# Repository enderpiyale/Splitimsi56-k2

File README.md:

# Splitimsi
 Regular keeb that can split

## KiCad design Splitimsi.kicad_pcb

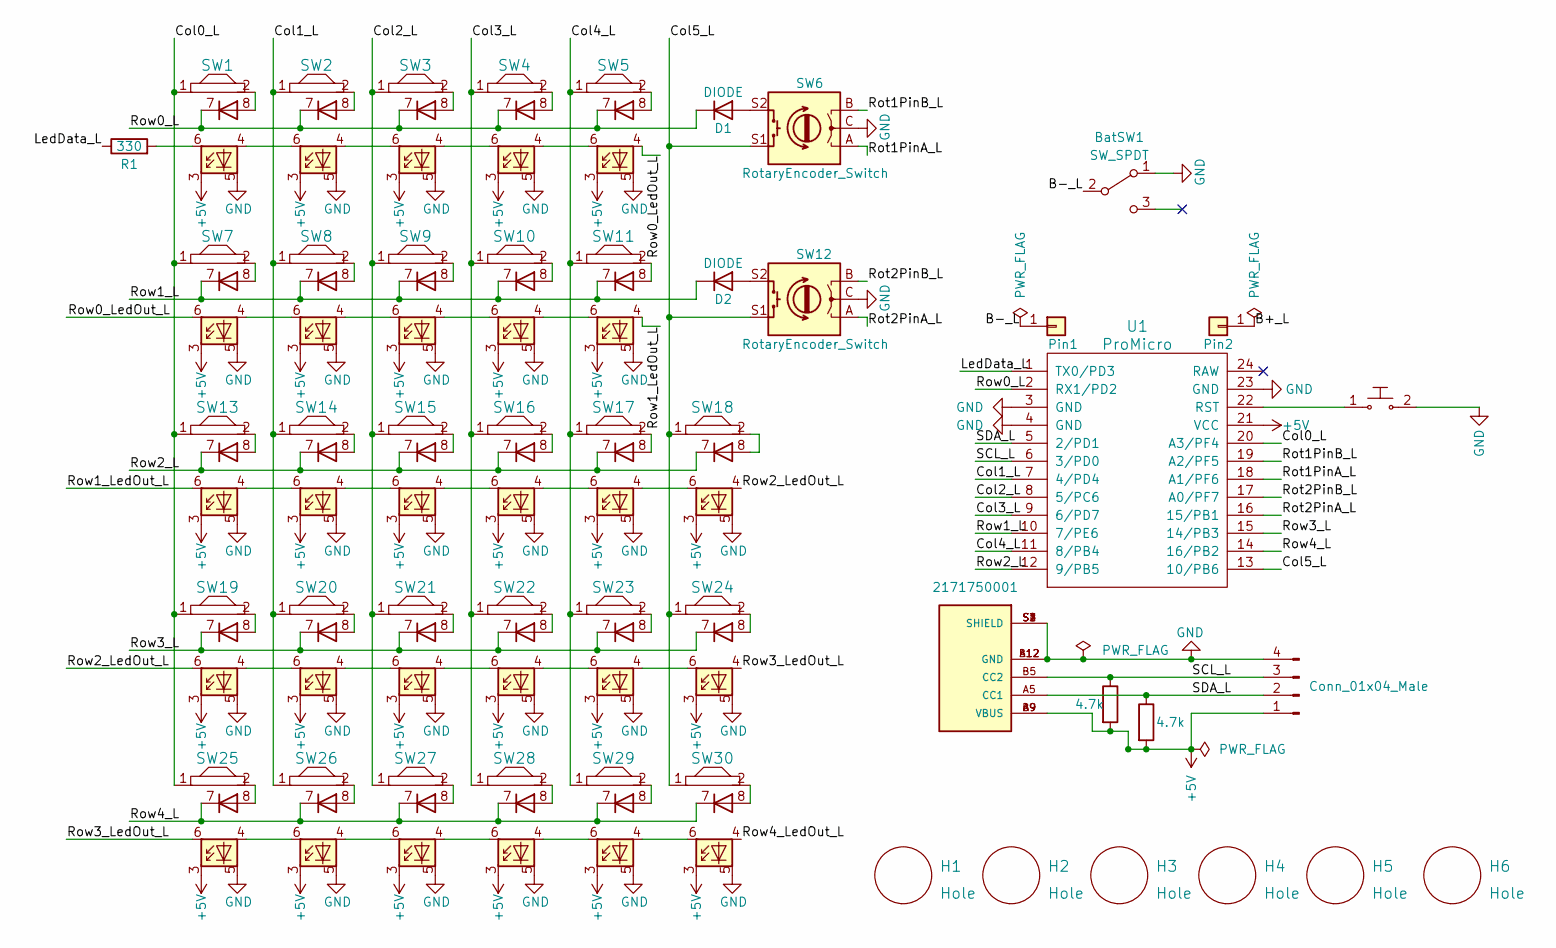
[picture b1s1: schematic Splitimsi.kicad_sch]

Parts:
BatSW1: SW_SPDT; MSK12C02
D1, D2: DIODE; D_SOD123
Dogo1: Conn_01x04_Male; PinSocket_1x04_P2.00mm_Vertical
H1, H2, H3, H4, H5, H6: Hole; Generic-Mounthole
J1: 2171750001; MOLEX_2171750001; PARTREV A1
Pin1, Pin2: Conn_01x01; SinglePad
R1: 330; R_1206_3216Metric_Pad1.30x1.75mm_HandSolder
R2, R3: 4.7k; R_1206_3216Metric_Pad1.30x1.75mm_HandSolder
SW1, SW2, SW3, SW4, SW7, SW8, SW9, SW10, SW11, SW13, SW14, SW15, SW16, SW17, SW18, SW19, SW20, SW21, SW22, SW23, SW24, SW25, SW26, SW27, SW28, SW29, SW30: MX_RGB; Kailh_HS_MX_LED
SW5: MX_RGB; Kailh_HS_MX_LED_option4
SW6, SW12: RotaryEncoder_Switch; RotaryEncoder_EC11
U1: ProMicro; ArduinoProMicro
rst1: MPN B3U-1000P; Digi-Key_PN SW1020CT-ND

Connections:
+5V: Dogo1.1, J1.A9 (VBUS), J1.B9 (VBUS), R2.2, R3.2, SW1.3 (VDD), SW2.3 (VDD), SW3.3 (VDD), SW4.3 (VDD), SW5.3 (VDD), SW7.3 (VDD), SW8.3 (VDD), SW9.3 (VDD), SW10.3 (VDD), SW11.3 (VDD), SW13.3 (VDD), SW14.3 (VDD), SW15.3 (VDD), SW16.3 (VDD), SW17.3 (VDD), SW18.3 (VDD), SW19.3 (VDD), SW20.3 (VDD), SW21.3 (VDD), SW22.3 (VDD), SW23.3 (VDD), SW24.3 (VDD), SW25.3 (VDD), SW26.3 (VDD), SW27.3 (VDD), SW28.3 (VDD), SW29.3 (VDD), SW30.3 (VDD), U1.21 (VCC)
/B+_L: Pin2.1
/B-_L: BatSW1.2 (B), Pin1.1
/Col0_L: SW1.1, SW7.1, SW13.1, SW19.1, SW25.1, U1.20 (A3/PF4)
/Col1_L: SW2.1, SW8.1, SW14.1, SW20.1, SW26.1, U1.7 (4/PD4)
/Col2_L: SW3.1, SW9.1, SW15.1, SW21.1, SW27.1, U1.8 (5/PC6)
/Col3_L: SW4.1, SW10.1, SW16.1, SW22.1, SW28.1, U1.9 (6/PD7)
/Col4_L: SW5.1, SW11.1, SW17.1, SW23.1, SW29.1, U1.11 (8/PB4)
/Col5_L: SW6.S1, SW12.S1, SW18.1, SW24.1, SW30.1, U1.13 (10/PB6)
/LedData_L: R1.1, U1.1 (TX0/PD3)
/Rot1PinA_L: SW6.A, U1.18 (A1/PF6)
/Rot1PinB_L: SW6.B, U1.19 (A2/PF5)
/Rot2PinA_L: SW12.A, U1.16 (15/PB1)
/Rot2PinB_L: SW12.B, U1.17 (A0/PF7)
/Row0_L: D1.2 (K), SW1.7 (K), SW2.7 (K), SW3.7 (K), SW4.7 (K), SW5.7 (K), U1.2 (RX1/PD2)
/Row0_LedOut_L: SW5.4 (DOUT), SW7.6 (DIN)
/Row1_L: D2.2 (K), SW7.7 (K), SW8.7 (K), SW9.7 (K), SW10.7 (K), SW11.7 (K), U1.10 (7/PE6)
/Row1_LedOut_L: SW11.4 (DOUT), SW13.6 (DIN)
/Row2_L: SW13.7 (K), SW14.7 (K), SW15.7 (K), SW16.7 (K), SW17.7 (K), SW18.7 (K), U1.12 (9/PB5)
/Row2_LedOut_L: SW18.4 (DOUT), SW19.6 (DIN)
/Row3_L: SW19.7 (K), SW20.7 (K), SW21.7 (K), SW22.7 (K), SW23.7 (K), SW24.7 (K), U1.15 (14/PB3)
/Row3_LedOut_L: SW24.4 (DOUT), SW25.6 (DIN)
/Row4_L: SW25.7 (K), SW26.7 (K), SW27.7 (K), SW28.7 (K), SW29.7 (K), SW30.7 (K), U1.14 (16/PB2)
/Row4_LedOut_L: SW30.4 (DOUT)
/SCL_L: Dogo1.3, J1.B5 (CC2), R2.1, U1.6 (3/PD0)
/SDA_L: Dogo1.2, J1.A5 (CC1), R3.1, U1.5 (2/PD1)
GND: BatSW1.1 (A), Dogo1.4, J1.A12 (GND), J1.B12 (GND), J1.S1 (SHIELD), J1.S2 (SHIELD), J1.S3 (SHIELD), J1.S4 (SHIELD), SW1.5 (GND), SW2.5 (GND), SW3.5 (GND), SW4.5 (GND), SW5.5 (GND), SW6.C, SW7.5 (GND), SW8.5 (GND), SW9.5 (GND), SW10.5 (GND), SW11.5 (GND), SW12.C, SW13.5 (GND), SW14.5 (GND), SW15.5 (GND), SW16.5 (GND), SW17.5 (GND), SW18.5 (GND), SW19.5 (GND), SW20.5 (GND), SW21.5 (GND), SW22.5 (GND), SW23.5 (GND), SW24.5 (GND), SW25.5 (GND), SW26.5 (GND), SW27.5 (GND), SW28.5 (GND), SW29.5 (GND), SW30.5 (GND), U1.3 (GND), U1.4 (GND), U1.23 (GND), rst1.2
unnamed: D1.1 (A), SW6.S2
unnamed: D2.1 (A), SW12.S2
unnamed: R1.2, SW1.6 (DIN)
unnamed: SW1.2, SW1.8 (A)
unnamed: SW1.4 (DOUT), SW2.6 (DIN)
unnamed: SW2.2, SW2.8 (A)
unnamed: SW2.4 (DOUT), SW3.6 (DIN)
unnamed: SW3.2, SW3.8 (A)
unnamed: SW3.4 (DOUT), SW4.6 (DIN)
unnamed: SW4.2, SW4.8 (A)
unnamed: SW4.4 (DOUT), SW5.6 (DIN)
unnamed: SW5.2, SW5.8 (A)
unnamed: SW7.2, SW7.8 (A)
unnamed: SW7.4 (DOUT), SW8.6 (DIN)
unnamed: SW8.2, SW8.8 (A)
unnamed: SW8.4 (DOUT), SW9.6 (DIN)
unnamed: SW9.2, SW9.8 (A)
unnamed: SW10.2, SW10.8 (A)
unnamed: SW10.4 (DOUT), SW11.6 (DIN)
unnamed: SW9.4 (DOUT), SW10.6 (DIN)
unnamed: SW11.2, SW11.8 (A)
unnamed: SW13.2, SW13.8 (A)
unnamed: SW13.4 (DOUT), SW14.6 (DIN)
unnamed: SW14.2, SW14.8 (A)
unnamed: SW14.4 (DOUT), SW15.6 (DIN)
unnamed: SW15.2, SW15.8 (A)
unnamed: SW15.4 (DOUT), SW16.6 (DIN)
unnamed: SW16.2, SW16.8 (A)
unnamed: SW16.4 (DOUT), SW17.6 (DIN)
unnamed: SW17.2, SW17.8 (A)
unnamed: SW17.4 (DOUT), SW18.6 (DIN)
unnamed: SW18.2, SW18.8 (A)
unnamed: SW19.2, SW19.8 (A)
unnamed: SW19.4 (DOUT), SW20.6 (DIN)
unnamed: SW20.2, SW20.8 (A)
unnamed: SW20.4 (DOUT), SW21.6 (DIN)
unnamed: SW21.2, SW21.8 (A)
unnamed: SW21.4 (DOUT), SW22.6 (DIN)
unnamed: SW22.2, SW22.8 (A)
unnamed: SW22.4 (DOUT), SW23.6 (DIN)
unnamed: SW23.2, SW23.8 (A)
unnamed: SW23.4 (DOUT), SW24.6 (DIN)
unnamed: SW24.2, SW24.8 (A)
unnamed: SW25.2, SW25.8 (A)
unnamed: SW25.4 (DOUT), SW26.6 (DIN)
unnamed: SW26.2, SW26.8 (A)
unnamed: SW26.4 (DOUT), SW27.6 (DIN)
unnamed: SW27.2, SW27.8 (A)
unnamed: SW27.4 (DOUT), SW28.6 (DIN)
unnamed: SW28.2, SW28.8 (A)
unnamed: SW28.4 (DOUT), SW29.6 (DIN)
unnamed: SW29.2, SW29.8 (A)
unnamed: SW29.4 (DOUT), SW30.6 (DIN)
unnamed: SW30.2, SW30.8 (A)
unnamed: U1.22 (RST), rst1.1

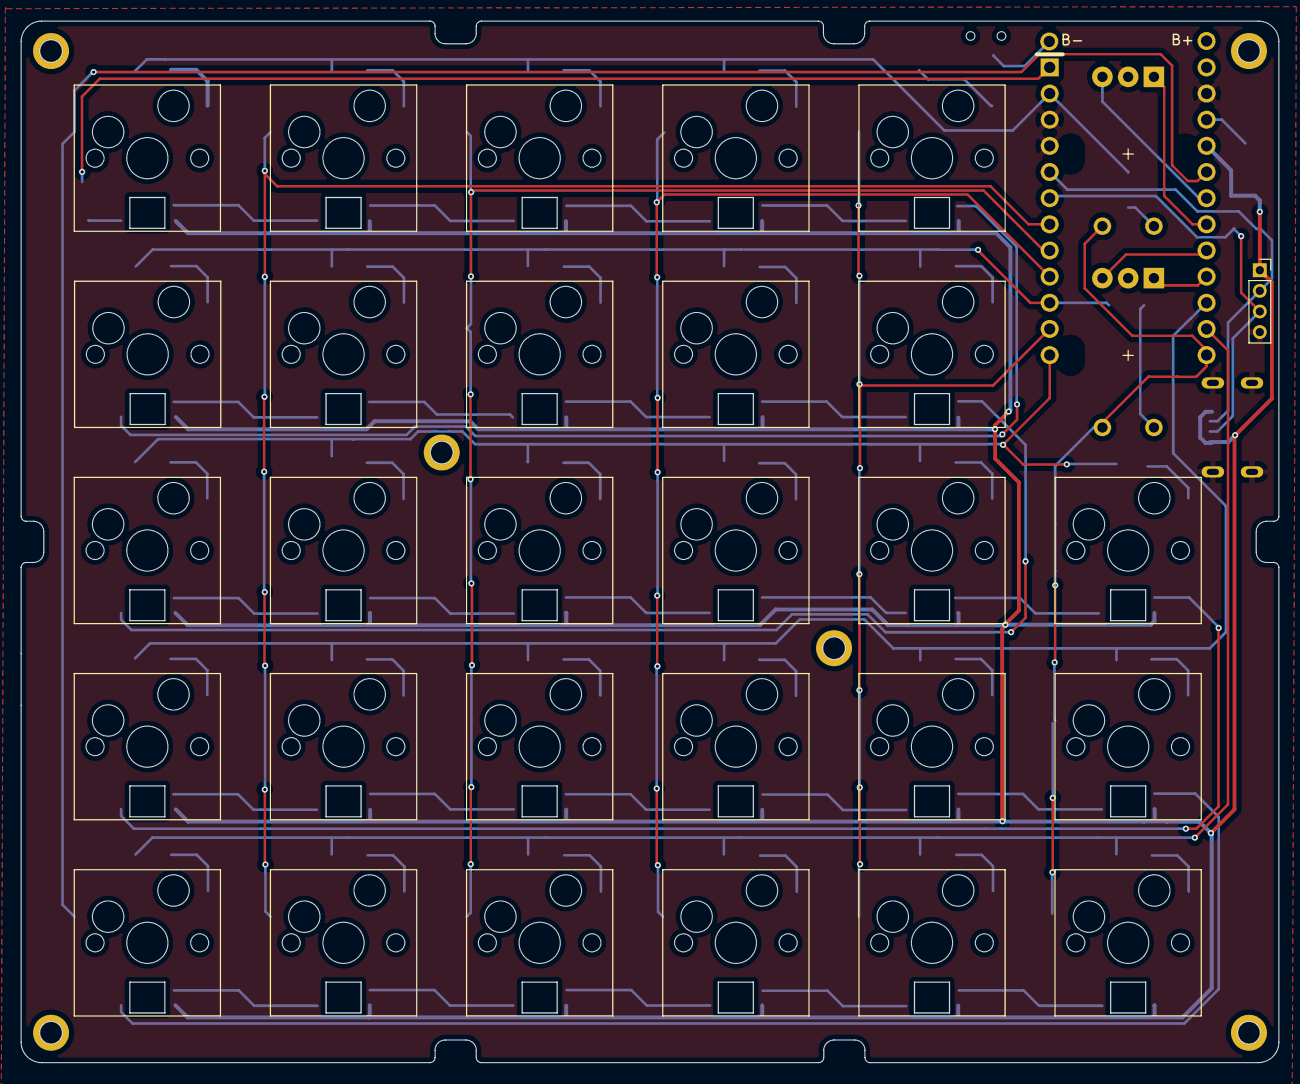
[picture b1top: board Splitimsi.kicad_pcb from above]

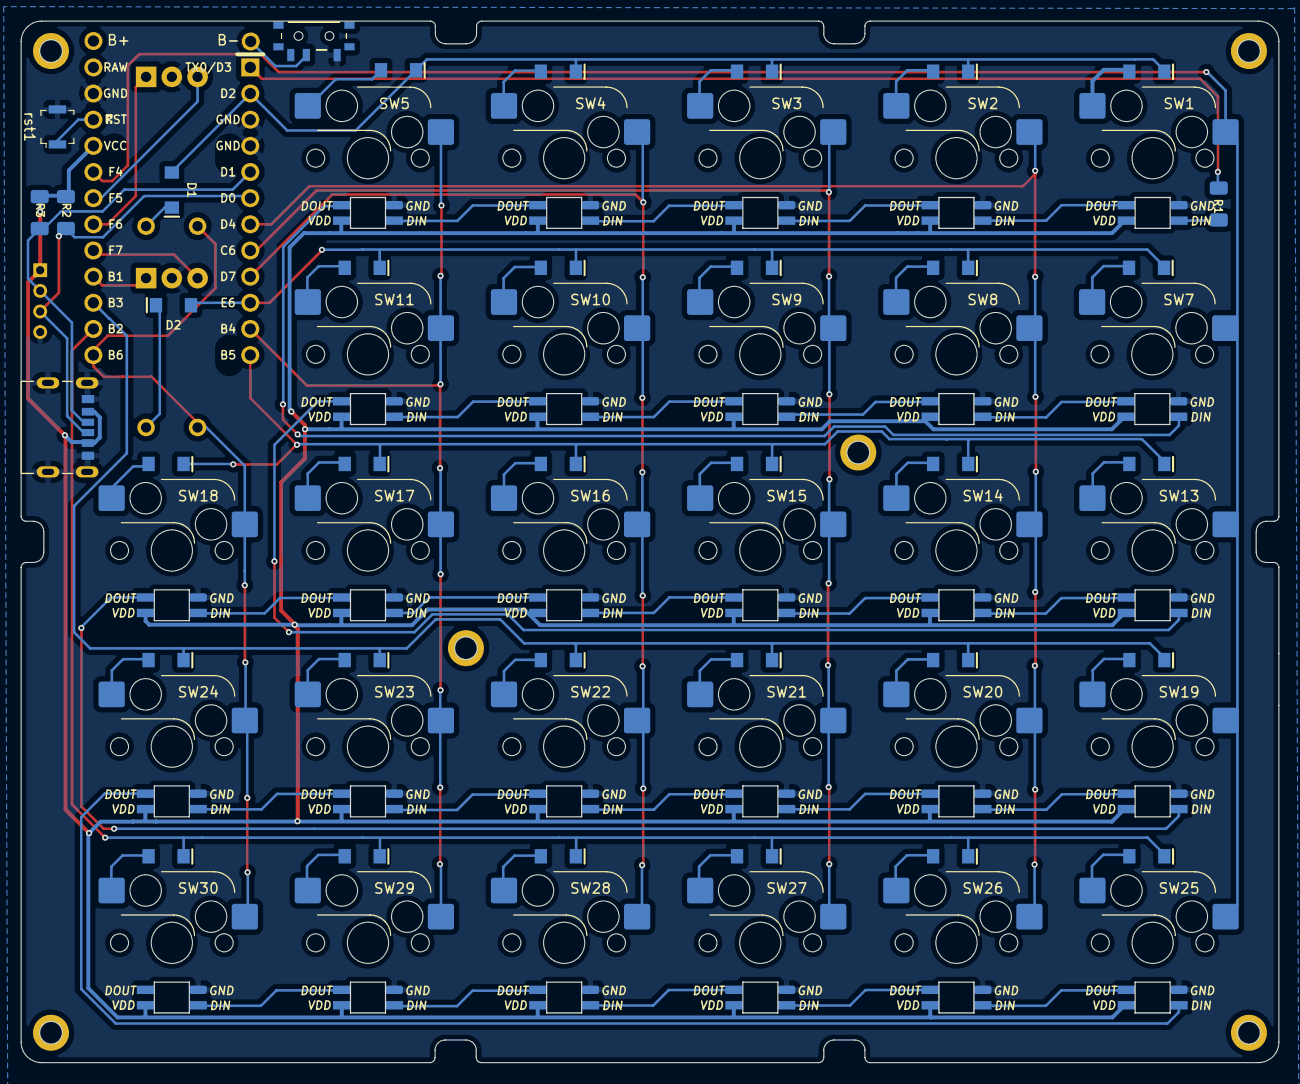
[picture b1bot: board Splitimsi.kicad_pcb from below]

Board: 2 copper layers, 122.1 x 101.1 mm, 48 parts (8 on the bottom side), 80 nets.

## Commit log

2022-08-16 First layout design
2022-08-16 Minor Adjustments
2022-08-17 diode 3d models added
2022-08-18 v0.3
    - Led footprints corrected and rearranged
    - Knob, Led, ProMicro, TRRS 3d models fine tuned
    - Led Labels added
    - Same row Leds connected
2022-08-18 Reset button schematic added
2022-08-18 Led test route added between row 4 and 5
2022-08-18 Led Connection added with via
2022-08-18 remove rst sw footprint
2022-08-18 Rows and Columns labels connected to the MCU
2022-08-19 tht diode footprints changed with smds
2022-08-19 Row tracks connected to the Mcu
2022-08-19 v0.5
    - rows and columns connected to the MCU
    - main tracks connected except rst button, knob, gnd, trrs
2022-08-19 fucked up update
    - ic2 resistors added
    - trrs tracks connected to the mcu
    - pin 5 and 6 deleted for column tracks
2022-08-20 TRRS resistors and footprints connected
2022-08-20 v0.6
    - PCB color changed to black
    - Courtyard error severity level changed to warnings
    - Line on edge cuts error level reduced to warnings
2022-08-21 Resistor footprints changed with 1206
2022-08-21 Front silkscreen creator and version info added
2022-08-21 Reset button footprint placed
2022-08-21 Knob added to sw annotations
2022-08-21 Reset switch sch and footprint fucked
2022-08-21 Reset button fixed
2022-08-21 Reset button footprint finalized
2022-08-22 trrs resistors places changed
2022-08-22 TRRS update
    - TRRS resistor tracks reorganized
    - Jack position reorganized
2022-08-22 Track bugs fixed
2022-08-23 GND zone fill added to the bottem zone
2022-08-23 mounting holes added
2022-08-24 Mounting hole test
2022-08-24 Mounting hole test 2
2022-08-24 unknown
2022-08-24 Mounting holes placed
2022-08-24 v0.8
    - GND zone fill completed.
    - Tracks reorganized
    - Board length from right increased
    - Board corner edge cuts rounded
2022-08-25 Oring test
2022-08-26 Edge cuts and pcb shape completed for oring design
2022-08-26 Component layout update
    - MCU footprint placed to the new edge
    - TRRS placed to the new edge
    - Trrs resistors reorganized
    - Tracks update
2022-08-26 Update Splitimsi.kicad_pcb
    RotPinB and Row3 mcu pin changed
2022-08-26 v0.9
    - Row schematics changed
    - Tracks reorganized
2022-08-26 mcu footprint flipped and tracks unconnected
2022-08-26 TRRS schematic, footprint and tracks. fixed
2022-08-26 GND Zone filled to bottom layer
2022-08-26 GND Zone fine tuned
2022-08-26 NO ERC Error
2022-08-26 pro micro 3d replaced
2022-08-26 svg step file outputs added
2022-08-26 gitignore
2022-08-26 border spaces increased
2022-08-26 Dogo connector added
2022-08-26 Dogo footprint update
2022-08-26 GND Zone reshaped
2022-08-26 Pro micro 3d model replaced
2022-08-26 Project rescued
2022-08-26 TRRS flipped to the back side
2022-08-26 serious layout update
    - mcu placed to back
    - new switch added to ex knob place
2022-08-27 Layout test
2022-08-27 rows and cols reorganized
2022-08-27 1 extra knob added to the layout
2022-08-27 TRRS footprınt changed to surface mount
2022-08-27 knob sockets tightened
2022-08-27 layout update
2022-08-27 Zone fill completed except reset button
2022-08-27 Temp reset button added
2022-08-27 Some ERC errors cleared
2022-08-27 Reset footprint changed
2022-08-27 reset button 3d view test
2022-08-28 Front layer GND fill zone added
2022-08-28 reset schematic changed
2022-08-28 slider switch added test
2022-08-29 Power Flags added
2022-08-29 battery pins added to the schematic and pcb
2022-08-29 Power flags added for battery and led powers connected to the battery
2022-08-29 b- and gnd zones added but not connected each other
2022-08-29 DRC errors cleared
2022-08-30 oring border length icnreased to 3.3mm
2022-08-30 MCU adjusted on pcb
2022-08-30 SW18 diode footprint adjusted
2022-08-30 Common ground zone fill for both sides
2022-09-06 Board dimension edited for oring
2022-09-10 Diode Silkscreen simplified
2022-09-10 Silkscreen overlap warning cleared
2022-09-10 MCU silkscreen simplified
2022-09-11 Board shape fine tuned for oring mount
2022-09-11 minor changes on trace
2022-09-11 Led DIN resistor added
2022-09-12 Led Power Supply connected to the MCU directly
2022-09-12 Reset button footprint changed
2022-09-16 trackball tests
2022-09-16 Battery on/off switch added
2022-09-16 minor track adjustments
2022-09-16 Battery SW 3D view added
2022-09-18 iBom file added
2022-09-18 _L added to indicate the left board to all track tags
2022-09-19 Led Vdd track connections updated to 90 degree
2022-09-19 diode tracks updated to 90 degree
2022-09-19 trrs jack adjustments
2022-09-19 TRRS adjustments
2022-09-20 Trrs position tests
2022-09-20 trrs removed usbc added
2022-09-21 usb sch, footprint and 3d added
2022-09-21 usbc tracks connected to the sda scl
2022-09-22 board dimension and i2c track updates
2022-09-22 Battery sw replaced
2022-09-22 sw18 diode 3d view fixed
2022-09-22 edge cut and component replacement fine tuned
2022-10-01 Layout dxf import
2022-10-01 3d view with the new layout
2022-10-03 gerbers added
2022-10-03 board details view added
2022-10-04 Update Splitimsi.kicad_pcb
    Column 5 Track adjusted
2022-10-04 gerbers new
